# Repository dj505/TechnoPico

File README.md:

# TechnoPico
## An advanced, customizable, and universal 18-button dance game controller
---
## **This project is ongoing! It's not quite ready yet.
Check in later to see when it's ready for release! You can keep up on [my Discord server](https://discord.gg/ctMByBy) or by messaging me directly.
---

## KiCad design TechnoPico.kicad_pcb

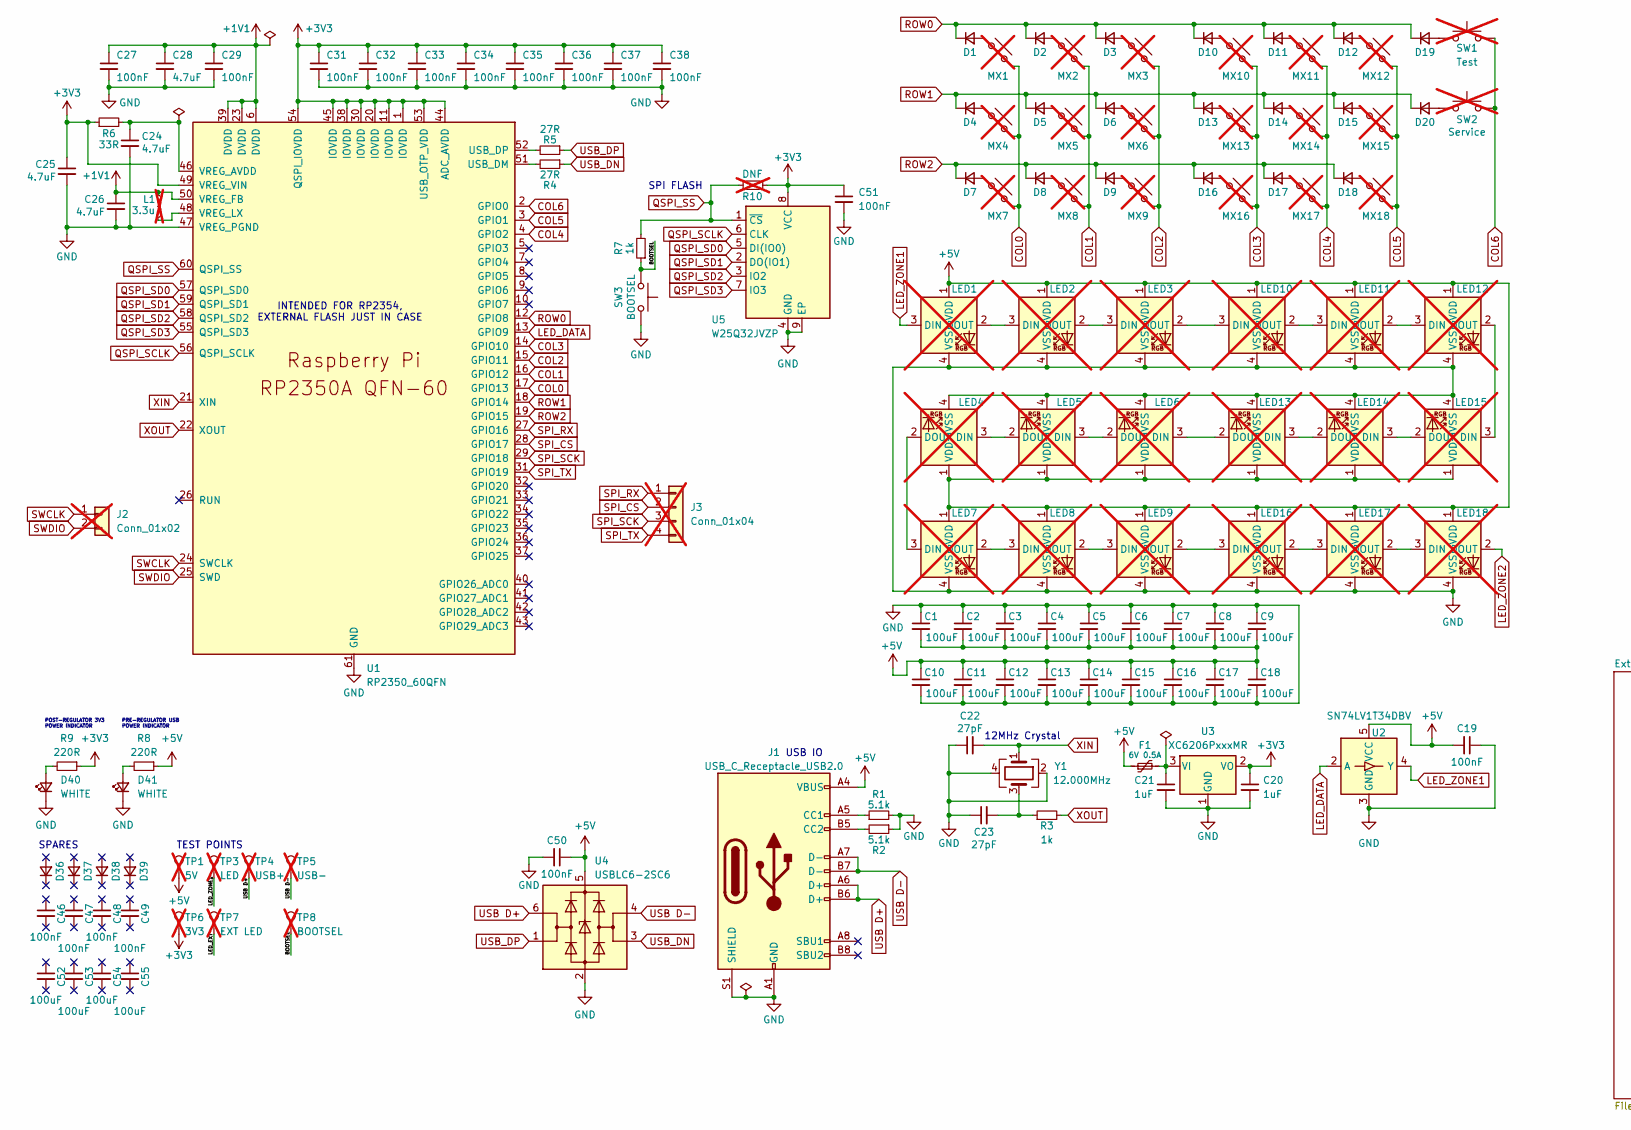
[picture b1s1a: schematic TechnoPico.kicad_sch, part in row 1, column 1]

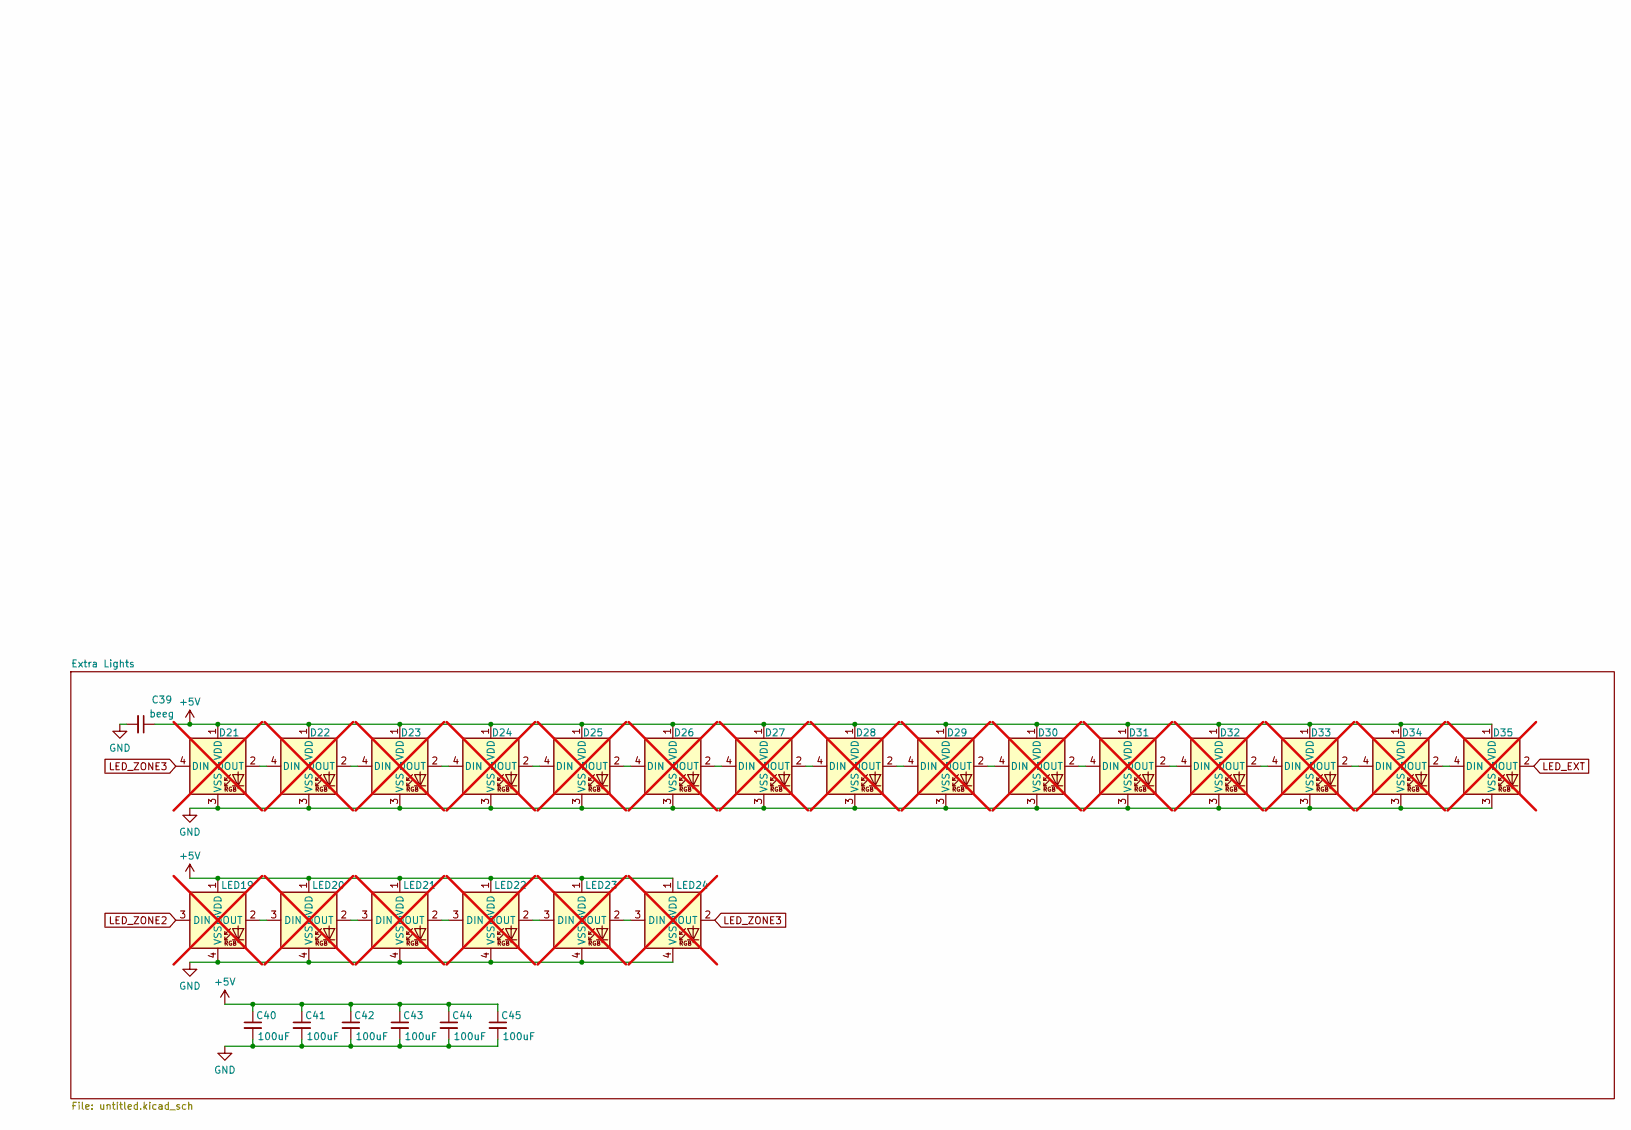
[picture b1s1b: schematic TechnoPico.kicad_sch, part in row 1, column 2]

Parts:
C1, C2, C3, C4, C5, C6, C7, C8, C9, C10, C11, C12, C13, C14, C15, C16, C17, C18, C40, C41, C42, C43, C44, C45, C52, C53, C54, C55: 100uF; C_1206_3216Metric; LCSC C15008
C19, C27, C29, C31, C32, C33, C34, C35, C36, C37, C38, C46, C47, C48, C49, C50, C51: 100nF; C_0402_1005Metric; LCSC C1525
C20, C21: 1uF; C_0402_1005Metric; LCSC C52923
C22, C23: 27pF; C_0402_1005Metric; LCSC C1557
C24, C28: 4.7uF; C_0402_1005Metric; LCSC C274416
C25, C26: 4.7uF; C_0402_1005Metric_small_pads; LCSC C274416
C39: beeg; C_1206_3216Metric; LCSC C15008
D1, D2, D3, D4, D5, D6, D7, D8, D9, D10, D11, D12, D13, D14, D15, D16, D17, D18, D19, D20, D36, D37, D38, D39: SOD-123; D_SOD-123; LCSC C81598
D21, D22, D23, D24, D25, D26, D27, D28, D29, D30, D31, D32, D33, D34, D35: WS2812B; LED_WS2812B-2020_PLCC4_2.0x2.0mm; not fitted
D40, D41: WHITE; LED_0603_1608Metric; LCSC C2290
F1: 6V 0.5A; Fuse_0603_1608Metric; LCSC C69688
J1: USB_C_Receptacle_USB2.0; USB_C_Receptacle_G-Switch_GT-USB-7010ASV; LCSC C2988369
J2: Conn_01x02; PinSocket_1x02_P1.27mm_Vertical; not fitted
J3: Conn_01x04; PinHeader_1x04_P1.27mm_Vertical; not fitted
L1: 3.3u; L_pol_2016; not fitted
LED1, LED2, LED3, LED7, LED8, LED9, LED10, LED11, LED12, LED16, LED17, LED18: MX_SK6812MINI-E; LED_MX_6028R-ROT; not fitted
LED4, LED5, LED6, LED13, LED14, LED15: MX_SK6812MINI-E; LED_MX_6028R; not fitted
LED19, LED20, LED21, LED22, LED23, LED24: MX_SK6812MINI-E; LED_6028R; not fitted
MX1, MX2, MX3, MX4, MX5, MX6, MX7, MX8, MX9, MX10, MX11, MX12, MX13, MX14, MX15, MX16, MX17, MX18: MX_SW_HS; SW_MX_HS_CPG151101S11_1u; not fitted
R1, R2: 5.1k; R_0402_1005Metric; LCSC C25905
R3, R7: 1k; R_0402_1005Metric; LCSC C106235
R4, R5: 27R; R_0402_1005Metric; LCSC C2909343
R6: 33R; R_0402_1005Metric; LCSC C138002
R8, R9: 220R; R_0402_1005Metric; LCSC C112291
R10: DNF; R_0402_1005Metric_Pad0.72x0.64mm_HandSolder; not fitted
SW1: Test; SW_Tactile_SPST_Angled_PTS645Vx39-2LFS; not fitted
SW2: Service; SW_Tactile_SPST_Angled_PTS645Vx39-2LFS; not fitted
SW3: BOOTSEL; SW_Push_1P1T_XKB_TS-1187A; LCSC C318884
TP1: 5V; TestPoint_Pad_D1.0mm; not fitted
TP3: LED; TestPoint_Pad_D1.0mm; not fitted
TP4: USB+; TestPoint_Pad_D1.0mm; not fitted
TP5: USB-; TestPoint_Pad_D1.0mm; not fitted
TP6: 3V3; TestPoint_Pad_D1.0mm; not fitted
TP7: EXT LED; TestPoint_Pad_D1.0mm; not fitted
TP8: BOOTSEL; TestPoint_Pad_D1.0mm; not fitted
U1: RP2350_60QFN; RP2350-QFN-60-1EP_7x7_P0.4mm_EP3.4x3.4mm_ThermalVias; LCSC C42411118
U2: SN74LV1T34DBV; SOT-23-5; LCSC C100024
U3: XC6206PxxxMR; SOT-23-3; LCSC C5446
U4: USBLC6-2SC6; SOT-23-6; LCSC C2687116
U5: W25Q32JVZP; WSON-8-1EP_6x5mm_P1.27mm_EP3.4x4.3mm; LCSC C571260
Y1: 12.000MHz; Crystal_SMD_3225-4Pin_3.2x2.5mm; LCSC C20625731

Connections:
+1V1: C26.1, C27.1, C28.1, C29.1, L1.1, U1.6 (DVDD), U1.23 (DVDD), U1.39 (DVDD), U1.50 (VREG_FB)
+3V3: C20.1, C25.1, C31.1, C32.1, C33.1, C34.1, C35.1, C36.1, C37.1, C38.1, C51.1, R6.1, R9.1, R10.1, TP6.1, U1.1 (IOVDD), U1.11 (IOVDD), U1.20 (IOVDD), U1.30 (IOVDD), U1.38 (IOVDD), U1.44 (ADC_AVDD), U1.45 (IOVDD), U1.49 (VREG_VIN), U1.53 (USB_OTP_VDD), U1.54 (QSPI_IOVDD), U3.2 (VO), U5.8 (VCC)
+5V: C1.2, C2.2, C3.2, C4.2, C5.2, C6.2, C7.2, C8.2, C9.2, C10.1, C11.1, C12.1, C13.1, C14.1, C15.1, C16.1, C17.1, C18.1, C19.2, C39.1, C40.1, C41.1, C42.1, C43.1, C44.1, C45.1, C50.1, D21.1 (VDD), D22.1 (VDD), D23.1 (VDD), D24.1 (VDD), D25.1 (VDD), D26.1 (VDD), D27.1 (VDD), D28.1 (VDD), D29.1 (VDD), D30.1 (VDD), D31.1 (VDD), D32.1 (VDD), D33.1 (VDD), D34.1 (VDD), D35.1 (VDD), F1.1, J1.A4 (VBUS), J1.A9 (VBUS), J1.B4 (VBUS), J1.B9 (VBUS), LED1.1 (VDD), LED2.1 (VDD), LED3.1 (VDD), LED4.1 (VDD), LED5.1 (VDD), LED6.1 (VDD), LED7.1 (VDD), LED8.1 (VDD), LED9.1 (VDD), LED10.1 (VDD), LED11.1 (VDD), LED12.1 (VDD), LED13.1 (VDD), LED14.1 (VDD), LED15.1 (VDD), LED16.1 (VDD), LED17.1 (VDD), LED18.1 (VDD), LED19.1 (VDD), LED20.1 (VDD), LED21.1 (VDD), LED22.1 (VDD), LED23.1 (VDD), LED24.1 (VDD), R8.1, TP1.1, U2.5 (VCC), U4.5 (VBUS)
/BOOTSEL: R7.1, SW3.1, TP8.1
COL0: MX1.2, MX4.2, MX7.2, U1.17 (GPIO13)
COL1: MX2.2, MX5.2, MX8.2, U1.16 (GPIO12)
COL2: MX3.2, MX6.2, MX9.2, U1.15 (GPIO11)
COL3: MX10.2, MX13.2, MX16.2, U1.14 (GPIO10)
COL4: MX11.2, MX14.2, MX17.2, U1.4 (GPIO2)
COL5: MX12.2, MX15.2, MX18.2, U1.3 (GPIO1)
COL6: SW1.2, SW2.2, U1.2 (GPIO0)
GND: C1.1, C2.1, C3.1, C4.1, C5.1, C6.1, C7.1, C8.1, C9.1, C10.2, C11.2, C12.2, C13.2, C14.2, C15.2, C16.2, C17.2, C18.2, C19.1, C20.2, C21.2, C22.1, C23.1, C24.2, C25.2, C26.2, C27.2, C28.2, C29.2, C31.2, C32.2, C33.2, C34.2, C35.2, C36.2, C37.2, C38.2, C39.2, C40.2, C41.2, C42.2, C43.2, C44.2, C45.2, C50.2, C51.2, D21.3 (VSS), D22.3 (VSS), D23.3 (VSS), D24.3 (VSS), D25.3 (VSS), D26.3 (VSS), D27.3 (VSS), D28.3 (VSS), D29.3 (VSS), D30.3 (VSS), D31.3 (VSS), D32.3 (VSS), D33.3 (VSS), D34.3 (VSS), D35.3 (VSS), D40.1 (K), D41.1 (K), J1.A1 (GND), J1.A12 (GND), J1.B1 (GND), J1.B12 (GND), J1.S1 (SHIELD), LED1.4 (VSS), LED2.4 (VSS), LED3.4 (VSS), LED4.4 (VSS), LED5.4 (VSS), LED6.4 (VSS), LED7.4 (VSS), LED8.4 (VSS), LED9.4 (VSS), LED10.4 (VSS), LED11.4 (VSS), LED12.4 (VSS), LED13.4 (VSS), LED14.4 (VSS), LED15.4 (VSS), LED16.4 (VSS), LED17.4 (VSS), LED18.4 (VSS), LED19.4 (VSS), LED20.4 (VSS), LED21.4 (VSS), LED22.4 (VSS), LED23.4 (VSS), LED24.4 (VSS), R1.2, R2.1, SW3.2, U1.47 (VREG_PGND), U1.61 (GND), U2.3 (GND), U3.1 (GND), U4.2 (GND), U5.4 (GND), U5.9 (EP), Y1.2, Y1.4
LED_DATA: U1.13 (GPIO9), U2.2 (A)
LED_EXT: D35.2 (DOUT), TP7.1
LED_ZONE1: LED1.3 (DIN), TP3.1, U2.4 (Y)
LED_ZONE2: LED18.2 (DOUT), LED19.3 (DIN)
LED_ZONE3: D21.4 (DIN), LED24.2 (DOUT)
unnamed: C23.2, R3.1, Y1.3
unnamed: D1.2 (A), MX1.1
unnamed: D2.2 (A), MX2.1
unnamed: D3.2 (A), MX3.1
unnamed: D4.2 (A), MX4.1
unnamed: D5.2 (A), MX5.1
unnamed: D6.2 (A), MX6.1
unnamed: D7.2 (A), MX7.1
unnamed: D8.2 (A), MX8.1
unnamed: D9.2 (A), MX9.1
unnamed: D10.2 (A), MX10.1
unnamed: D11.2 (A), MX11.1
unnamed: D12.2 (A), MX12.1
unnamed: D13.2 (A), MX13.1
unnamed: D14.2 (A), MX14.1
unnamed: D15.2 (A), MX15.1
unnamed: D16.2 (A), MX16.1
unnamed: D17.2 (A), MX17.1
unnamed: D18.2 (A), MX18.1
unnamed: D19.2 (A), SW1.1
unnamed: D20.2 (A), SW2.1
unnamed: D21.2 (DOUT), D22.4 (DIN)
unnamed: D22.2 (DOUT), D23.4 (DIN)
unnamed: D23.2 (DOUT), D24.4 (DIN)
unnamed: D24.2 (DOUT), D25.4 (DIN)
unnamed: D25.2 (DOUT), D26.4 (DIN)
unnamed: D26.2 (DOUT), D27.4 (DIN)
unnamed: D27.2 (DOUT), D28.4 (DIN)
unnamed: D28.2 (DOUT), D29.4 (DIN)
unnamed: D29.2 (DOUT), D30.4 (DIN)
unnamed: D30.2 (DOUT), D31.4 (DIN)
unnamed: D31.2 (DOUT), D32.4 (DIN)
unnamed: D32.2 (DOUT), D33.4 (DIN)
unnamed: D33.2 (DOUT), D34.4 (DIN)
unnamed: D34.2 (DOUT), D35.4 (DIN)
unnamed: D40.2 (A), R9.2
unnamed: D41.2 (A), R8.2
unnamed: J1.A5 (CC1), R1.1
unnamed: J1.B5 (CC2), R2.2
unnamed: LED1.2 (DOUT), LED2.3 (DIN)
unnamed: LED2.2 (DOUT), LED3.3 (DIN)
unnamed: LED4.3 (DIN), LED5.2 (DOUT)
unnamed: LED4.2 (DOUT), LED7.3 (DIN)
unnamed: LED5.3 (DIN), LED6.2 (DOUT)
unnamed: LED7.2 (DOUT), LED8.3 (DIN)
unnamed: LED8.2 (DOUT), LED9.3 (DIN)
unnamed: LED3.2 (DOUT), LED10.3 (DIN)
unnamed: LED10.2 (DOUT), LED11.3 (DIN)
unnamed: LED11.2 (DOUT), LED12.3 (DIN)
unnamed: LED12.2 (DOUT), LED15.3 (DIN)
unnamed: LED13.3 (DIN), LED14.2 (DOUT)
unnamed: LED6.3 (DIN), LED13.2 (DOUT)
unnamed: LED14.3 (DIN), LED15.2 (DOUT)
unnamed: LED9.2 (DOUT), LED16.3 (DIN)
unnamed: LED16.2 (DOUT), LED17.3 (DIN)
unnamed: LED17.2 (DOUT), LED18.3 (DIN)
unnamed: LED19.2 (DOUT), LED20.3 (DIN)
unnamed: LED20.2 (DOUT), LED21.3 (DIN)
unnamed: LED21.2 (DOUT), LED22.3 (DIN)
unnamed: LED22.2 (DOUT), LED23.3 (DIN)
unnamed: LED23.2 (DOUT), LED24.3 (DIN)
unnamed: R4.2, U1.51 (USB_DM)
unnamed: R5.2, U1.52 (USB_DP)
unnamed: C24.1, R6.2, U1.46 (VREG_AVDD)
unnamed: L1.2, U1.48 (VREG_LX)
unnamed: C21.1, F1.2, U3.3 (VI)
QSPI_SCLK: U1.56 (QSPI_SCLK), U5.6 (CLK)
QSPI_SD0: U1.57 (QSPI_SD0), U5.5 (DI(IO0))
QSPI_SD1: U1.59 (QSPI_SD1), U5.2 (DO(IO1))
QSPI_SD2: U1.58 (QSPI_SD2), U5.3 (IO2)
QSPI_SD3: U1.55 (QSPI_SD3), U5.7 (IO3)
QSPI_SS: R7.2, R10.2, U1.60 (QSPI_SS), U5.1 (~CS)
ROW0: D1.1 (K), D2.1 (K), D3.1 (K), D10.1 (K), D11.1 (K), D12.1 (K), D19.1 (K), U1.12 (GPIO8)
ROW1: D4.1 (K), D5.1 (K), D6.1 (K), D13.1 (K), D14.1 (K), D15.1 (K), D20.1 (K), U1.18 (GPIO14)
ROW2: D7.1 (K), D8.1 (K), D9.1 (K), D16.1 (K), D17.1 (K), D18.1 (K), U1.19 (GPIO15)
SPI_CS: J3.2, U1.28 (GPIO17)
SPI_RX: J3.1, U1.27 (GPIO16)
SPI_SCK: J3.3, U1.29 (GPIO18)
SPI_TX: J3.4, U1.31 (GPIO19)
SWCLK: J2.1, U1.24 (SWCLK)
SWDIO: J2.2, U1.25 (SWD)
USB D+: J1.A6 (D+), J1.B6 (D+), TP4.1, U4.6 (I/O1)
USB D-: J1.A7 (D-), J1.B7 (D-), TP5.1, U4.4 (I/O2)
USB_DN: R4.1, U4.3 (I/O2)
USB_DP: R5.1, U4.1 (I/O1)
XIN: C22.2, U1.21 (XIN), Y1.1
XOUT: R3.2, U1.22 (XOUT)

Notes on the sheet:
SPI FLASH
PRE-REGULATOR USB POWER INDICATOR
INTENDED FOR RP2354, EXTERNAL FLASH JUST IN CASE
12MHz Crystal
USB IO
POST-REGULATOR 3V3 POWER INDICATOR
TEST POINTS
SPARES

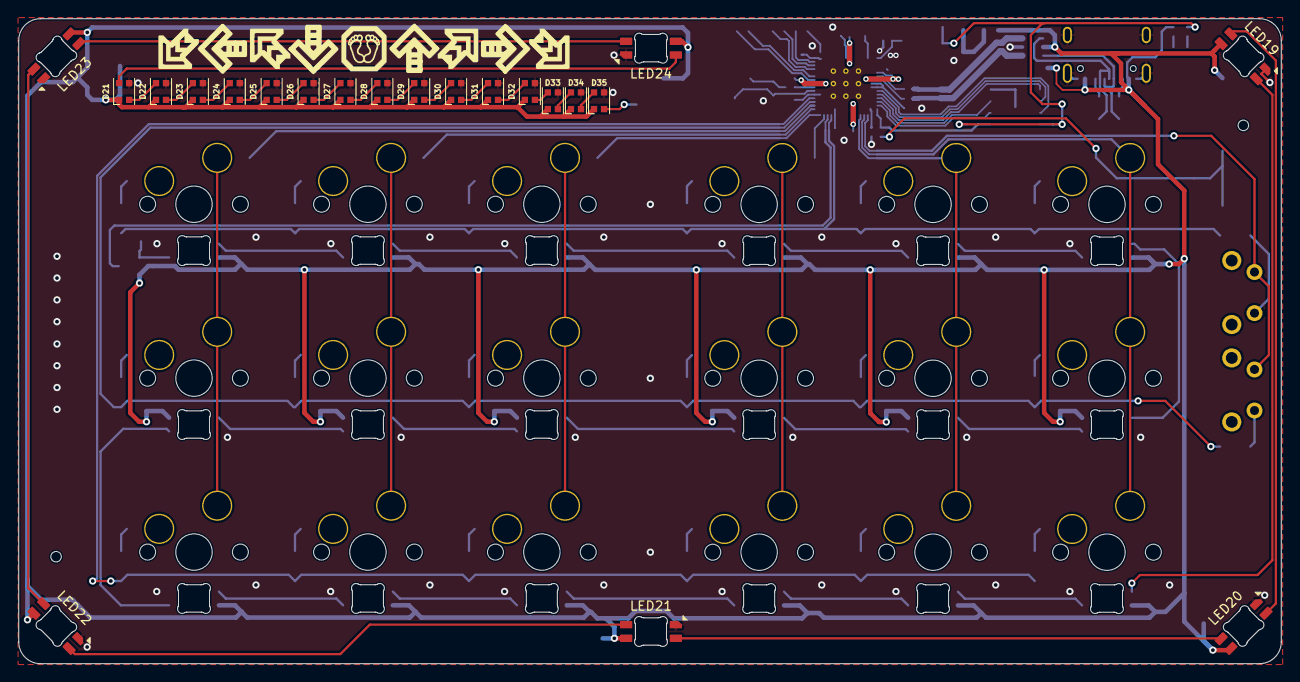
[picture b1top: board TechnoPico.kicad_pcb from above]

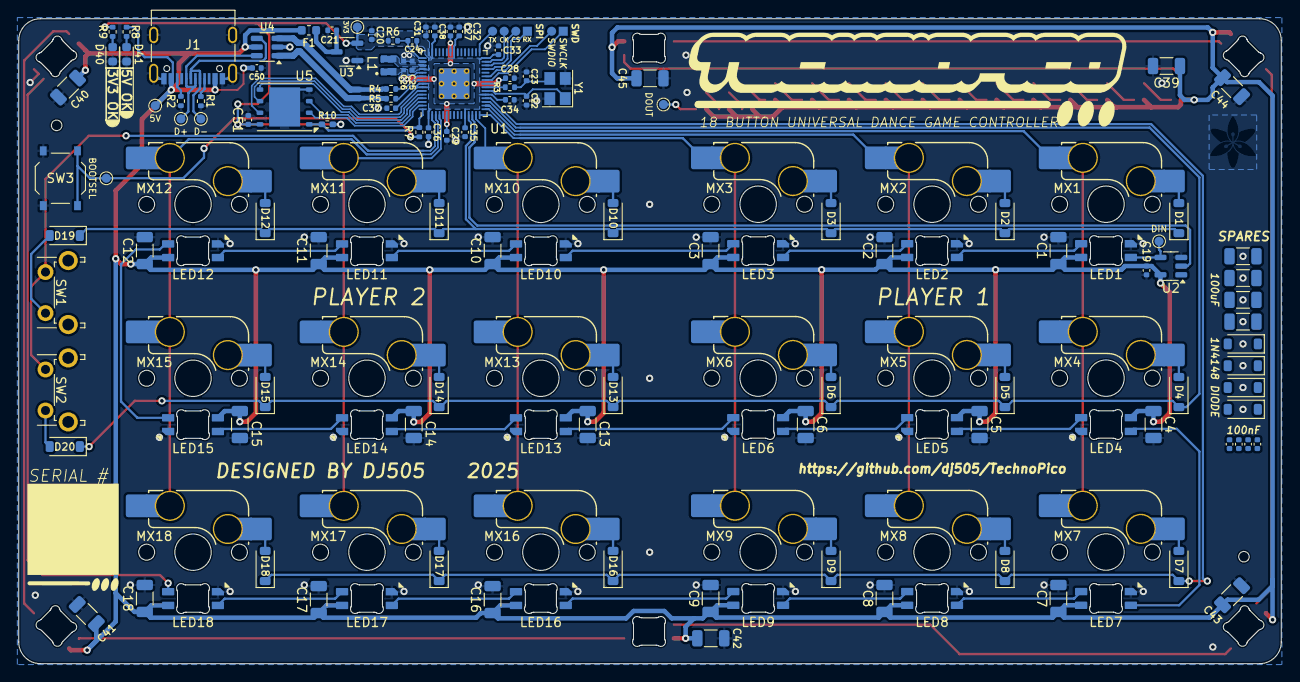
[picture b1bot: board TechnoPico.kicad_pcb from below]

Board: 2 copper layers, 138.3 x 70.6 mm, 168 parts (147 on the bottom side), 104 nets.

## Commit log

2024-10-29 Initial commit (oops already made the whole thing)
2024-10-30 Experimental corner cutouts for mounting
2024-10-30 Revert main PCB corner cutouts, add holes to plate
2025-01-12 Add flash
2025-01-12 Reroute 5V to LEDs to split up the ground plane less, etc
2025-01-12 Finishing touches
2025-01-13 Routing changes, use custom RP2350 inductor, etc
